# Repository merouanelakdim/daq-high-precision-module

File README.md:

🌟 High‑Precision Data Acquisition Module (DAQ)

A compact and robust 4‑channel data acquisition module designed with a strong focus on signal integrity, low noise, and clean analog/digital separation.
Built around an STM32 microcontroller, an analog multiplexer, and carefully tuned RC filtering, this board is engineered for reliable and accurate measurements.

🚀 Features
4 multiplexed analog input channels

STM32 microcontroller for fast sampling and processing

Optimized RC filter (R4/C9) for ADC input stabilization

Clean analog/digital domain separation

UART interface for communication

SWD interface for programming and debugging

2‑layer PCB designed with KiCad

Low‑noise power architecture with ferrite bead isolation

🧩 Hardware Architecture
Analog Front-End

4 input channels

Multiplexer for channel selection

RC low‑pass filter to stabilize ADC readings

Digital Core

STM32 MCU

SPI communication

UART interface

SWD programming header

Power Section

5V input

3.3V regulation

Analog/digital power separation

Decoupling and filtering for noise reduction

📁 Repository Structure
Code
📦 daq-high-precision-module
 ┣ 📂 hardware/        → KiCad project files (schematic + PCB)
 ┗ 📜 README.md        → You are here
🖼️ PCB Preview

🎯 Project Goals
Build a compact and reliable DAQ module

Ensure clean analog signal acquisition

Apply professional PCB design practices

Optimize routing for low noise and stability

Provide a reusable hardware platform for future projects

🛠️ Tools & Technologies
KiCad 8 for schematic and PCB design

STM32 ecosystem

LTspice for analog simulation

Git & GitHub for version control

👤 Author
Merouane Lakdim  
Embedded Electronics Engineer — Paris, France
Passionate about hardware design, signal integrity, and embedded systems.

📄 License
This project is licensed under the **MIT License**. See the [LICENSE](LICENSE) file for details.

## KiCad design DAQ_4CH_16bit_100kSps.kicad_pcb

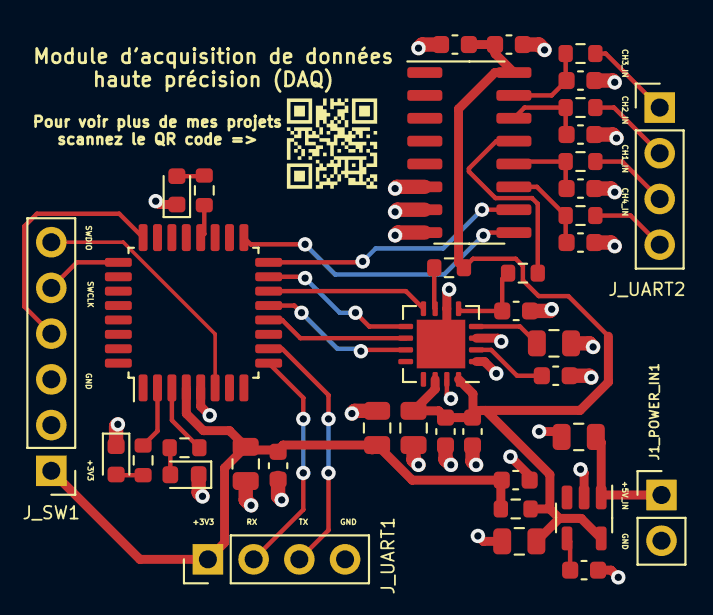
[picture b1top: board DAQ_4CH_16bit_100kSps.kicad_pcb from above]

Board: 2 copper layers, 40 parts (0 on the bottom side), 35 nets.

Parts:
C0, C6, C7: 4.7 µF; C_0805_2012Metric
C1, C2, C3, C4, C8, C10, C11, C12, C13, C14: 100 nF; C_0603_1608Metric
C5: 10 µF; C_0805_2012Metric
C9: 220 pF; C_0603_1608Metric
CBYP1: 10 nF; C_0603_1608Metric
CIN1: 1 µF; C_0805_2012Metric
COUT1: 10 µF; C_0805_2012Metric
Cdec1: 100 nF; C_0603_1608Metric
D1, D2, D3: LED; LED_0603_1608Metric
FB1: FerriteBead; R_0603_1608Metric
J1_POWER_IN1: Conn_01x02; PinHeader_1x02_P2.54mm_Vertical
J_SW1: Conn_01x06; PinHeader_1x06_P2.54mm_Vertical
J_UART1, J_UART2: Conn_01x04; PinHeader_1x04_P2.54mm_Vertical
R1, R2, R3, R6, R7, R8, R9: 1 kΩ; R_0603_1608Metric
R4: 33 Ω; R_0603_1608Metric
R5: 10 kΩ; R_0603_1608Metric
U1: LT1763‑3.3; SOT-23-5
U2: STM32G0B1KBTx; LQFP-32_7x7mm_P0.8mm
U3: ADS8681RUM; QFN-16-1EP_4x4mm_P0.65mm_EP2.7x2.7mm
U5: CD4052B; SOIC-16_3.9x9.9mm_P1.27mm

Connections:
+3V3_ANA: C2.1, C7.1, C8.2, C10.1, COUT1.1, Cdec1.2, FB1.1, R5.2, U1.5 (OUT), U3.14 (DVDD), U3.16 (AVDD), U5.16 (VDD)
+3V3_DIG: C0.1, C1.2, C4.1, C5.1, FB1.2, J_SW1.1, J_UART1.1, U2.4 (VDD)
+5V_IN: CIN1.1, J1_POWER_IN1.1, U1.1 (IN)
CH1_FILT: C11.2, R6.2, U5.12 (X0)
CH1_IN: J_UART2.3, R6.1
CH2_FILT: C12.2, R7.2, U5.14 (X1)
CH2_IN: J_UART2.2, R7.1
CH3_FILT: C13.2, R8.2, U5.15 (X2)
CH3_IN: J_UART2.1, R8.1
CH4_FILT: C14.2, R9.2, U5.11 (X3)
CH4_IN: J_UART2.4, R9.1
GND: C0.2, C1.1, C2.2, C3.2, C4.2, C5.2, C6.1, C7.2, C8.1, C9.1, C10.2, C11.1, C12.1, C13.1, C14.1, CBYP1.2, CIN1.2, COUT1.2, Cdec1.1, D1.1 (K), D2.1 (K), D3.1 (K), J1_POWER_IN1.2, J_SW1.3, J_UART1.4, U1.2 (GND), U2.5 (VSS), U3.1 (AGND), U3.3 (REFGND), U3.6 (AIN_GND), U3.15 (DGND), U3.17 (PAD), U5.6 (INH), U5.7 (VEE), U5.8 (VSS)
MUX_OUT: R4.1, U5.13 (X)
MUX_S0: U2.16 (PB1), U5.10 (A)
MUX_S1: U2.17 (PB2), U5.9 (B)
unnamed: D1.2 (A), R1.1
unnamed: D2.2 (A), R2.1
unnamed: D3.2 (A), R3.1
unnamed: J_SW1.4, U2.24 (PA13)
unnamed: J_SW1.5, U2.25 (PA14)
unnamed: J_SW1.6, U2.6 (PF2)
unnamed: J_UART1.2, U2.9 (PA2)
unnamed: J_UART1.3, U2.10 (PA3)
unnamed: CBYP1.1, U1.4 (BP)
unnamed: R1.2, U2.20 (PC6)
unnamed: R2.2, U2.2 (PC14)
unnamed: R3.2, U2.3 (PC15)
unnamed: C9.2, R4.2, U3.5 (AIN_P)
unnamed: C6.2, U3.4 (REFCAP)
unnamed: C3.1, U3.2 (REFIO)
unnamed: R5.1, U3.7 (~RST)
SPI_CS_ADC: U2.15 (PB0), U3.9 (CONVST/~CS)
SPI_MISO: U2.13 (PA6), U3.11 (SDO-0)
SPI_MOSI: U2.14 (PA7), U3.8 (SDI)
SPI_SCK: U2.12 (PA5), U3.10 (SCLK)

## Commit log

2026-02-08 Initial commit – DAQ high precision PCB
2026-02-08 Initialize README with project details and features
    Added detailed project description, features, architecture, goals, tools, and author information.
2026-02-08 Add MIT License to the project
2026-02-08 Update README with license details and remove image
    Removed outdated PCB image and updated license information.
2026-02-08 Add PCB preview image and project goals section
    Added a second PCB preview image and updated project goals.

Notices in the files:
README.md:
License: MIT
